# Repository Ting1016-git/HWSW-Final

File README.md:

# Smart Kitchen Guide

## Project Overview

**Smart Kitchen Guide** is a two-device cooking assistance system designed to help beginners master temperature control in cooking - from Chinese stir-frying to Western pan-searing. The system consists of a **Smart Handle Clip (Sensing Device)** that clamps onto any pan handle and monitors temperatures using triple sensing technology, and a **Cooking Terminal (Display Device)** that provides visual feedback through a stepper motor-driven gauge, LED indicators, and recipe guidance.

The sensing device wirelessly transmits temperature data to the display device, which uses a predictive algorithm to estimate when the target temperature will be reached and alerts the user at the optimal moment to add ingredients.

### Key Features

- **Triple Temperature Sensing**: Pan surface (IR), oil temperature (IR), and food internal temperature (K-type probe)
- **Universal Compatibility**: Spring-clip design fits handles from 15-40mm diameter
- **Open-Pan Cooking**: Perfect for stir-frying and sautéing without blocking the view
- **Wireless BLE Communication**: Real-time data transmission at 10Hz

### General Sketch

**Physical Features:**
- **Smart Handle Clip**: Spring-loaded clamp with OLED display, IR temperature sensor pointing toward pan body, detachable K-type thermocouple probe, and USB-C rechargeable battery
- **Cooking Terminal**: Retro radio-style desktop unit featuring a large circular temperature gauge with stepper motor-driven needle, RGB LED ring, OLED recipe display, and three tactile buttons (Select/Confirm/Back)

---

## Sensing Device: Smart Handle Clip

### Device Description

The Smart Handle Clip is a portable, clip-on temperature monitoring device that attaches to any pan or wok handle. It features **triple temperature sensing capability**:

1. **Infrared (IR) Sensor** - Non-contact measurement of pan surface and oil temperature
2. **K-Type Thermocouple Probe** - Detachable probe for measuring food internal temperature

The clip-on design allows the pan to remain open during cooking, making it ideal for Chinese stir-frying and Western sautéing where visual monitoring is essential.

### Detailed Sketch

### How It Works

1. **MLX90614 IR sensor** (mounted on bottom jaw, pointing toward pan) measures pan surface temperature from -70°C to +380°C without contact
2. The same IR sensor can measure **oil surface temperature** when the user aims it at the oil (mode switchable via button)
3. **Detachable K-type thermocouple probe** connects via port on the side for measuring food internal temperature (e.g., checking if meat is cooked through)
4. **MAX31855** thermocouple amplifier digitizes the probe signal via SPI
5. **ESP32-C3** microcontroller processes all sensor data at 10Hz and transmits via BLE
6. **0.96" OLED display** shows real-time temperature readings locally
7. **3 Status LEDs** indicate: Green (ready), Yellow (heating), Red (warning/overheat)
8. **500mAh Li-Po battery** provides ~8 hours of operation with USB-C charging

### Components & Part Numbers

| Component | Part Number | Description |
|-----------|-------------|-------------|
| Microcontroller | **ESP32-C3-MINI-1** | WiFi/BLE MCU, low power, SPI/I2C support |
| IR Temperature Sensor | **MLX90614ESF-BAA** | Non-contact IR thermometer, -70°C to +380°C, I2C |
| Thermocouple Sensor | **K-Type Thermocouple Probe** | Detachable, -50°C to +300°C, food-grade stainless steel |
| Thermocouple Amplifier | **MAX31855KASA+T** | Cold-junction compensated, SPI interface |
| OLED Display | **SSD1306 0.96" 128x64** | I2C interface, low power |
| Status LEDs | **0603 SMD LED** | Green, Yellow, Red (x3) |
| Battery | **Li-Po 502535** | 3.7V 500mAh rechargeable |
| Voltage Regulator | **AP2112K-3.3** | 3.3V LDO, 600mA output |
| Charging IC | **TP4056** | 1A Linear Li-ion charger, USB-C |
| Buttons | **TS-1109S** | 6x6mm SMD tact switch (x2: Power, Mode) |

## Display Device: Cooking Terminal

### Device Description

The Cooking Terminal is a desktop unit that receives temperature data from the Smart Handle Clip and provides rich visual feedback. The centerpiece is a large analog-style gauge with a stepper motor-driven needle showing current temperature. An RGB LED ring around the gauge indicates cooking status (heating/ready/overheating), while an OLED screen displays recipe steps and timing information. Users interact via three tactile buttons and can navigate through pre-loaded recipes.

### Detailed Sketch

### How It Works

1. The **ESP32-S3** receives temperature data via BLE from the Smart Handle Clip
2. Temperature prediction algorithm estimates time-to-target based on heating rate
3. The **28BYJ-48 stepper motor** drives the gauge needle to indicate current temperature (0-300°C scale)
4. **WS2812B RGB LED ring** shows status: blue (cold), green (heating), amber (target reached), red (overheating)
5. **1.3" OLED display** shows recipe name, current step, target temperature, and countdown timer
6. Three **tactile buttons** allow navigation: Select (◀), Confirm (✓), Back (↩)
7. **Buzzer** provides audio alerts when target temperature is reached
8. Powered by **18650 Li-ion battery** with USB-C charging

### Components & Part Numbers

| Component | Part Number | Description |
|-----------|-------------|-------------|
| Microcontroller | **ESP32-S3-WROOM-1** | Dual-core, BLE 5.0, sufficient GPIO |
| Stepper Motor | **28BYJ-48** | 5V unipolar, 64:1 gear ratio |
| Stepper Driver | **ULN2003A** | Darlington array driver |
| RGB LED Ring | **WS2812B 16-LED Ring** | Addressable RGB, 5V |
| OLED Display | **SH1106 1.3" 128x64** | I2C interface |
| Tactile Buttons | **TS-1109S** | 6x6mm SMD tact switch (x3) |
| Buzzer | **MLT-5020** | 5V active buzzer |
| Battery | **NCR18650B** | 3.7V 3400mAh Li-ion |
| Battery Charger | **TP4056 Module** | USB-C Li-ion charger with protection |
| Voltage Regulator | **AMS1117-3.3** | 3.3V LDO for logic |
| 5V Boost | **MT3608** | Step-up converter for motor/LED |

## System Communication & Architecture

### Communication Diagram

The Smart Handle Clip and Cooking Terminal communicate via **Bluetooth Low Energy (BLE)**:

- **Protocol**: BLE 5.0 with custom GATT service
- **Update Rate**: 10 Hz (100ms intervals)
- **Range**: Up to 10 meters (typical kitchen environment)
- **Latency**: < 50ms end-to-end

### System Block Diagram

```
┌─────────────────────────────────────────────────────────────────────────────────────┐
│                                 SYSTEM OVERVIEW                                     │
│                                                                                     │
│                                                                                     │
│    ┌──────────────────────┐                         ┌──────────────────────┐        │
│    │                      │                         │                      │        │
│    │   SENSING DEVICE     │      BLE 5.0 Link       │   DISPLAY DEVICE     │        │
│    │  (Smart Handle Clip) │ ═══════════════════════►│  (Cooking Terminal)  │        │
│    │                      │      10Hz, <50ms        │                      │        │
│    │                      │                         │                      │        │
│    └──────────────────────┘                         └──────────────────────┘        │
│                                                                                     │
│                                                                                     │
└─────────────────────────────────────────────────────────────────────────────────────┘
```

---

## Sensing Device (Smart Handle Clip)

```
┌─────────────────────────────────────────────────────────────────────────────────────┐
│                        SMART HANDLE CLIP (Sensing Device)                           │
│                                                                                     │
│                                                                                     │
│    ┌──────────────┐                             ┌──────────────┐                    │
│    │  MLX90614    │                             │ Xiao         │                    │
│    │  IR Sensor   ├──────────────┐      ┌───────┤ ESP32-C3     │                    │
│    │  (I2C)       │              │      │       │ (BLE TX)     │                    │
│    └──────────────┘              │      │       └───────┬──────┘                    │
│                                  │      │               │                           │
│                                  ▼      ▼               │                           │
│                              ┌──────────────┐           │          BLE 5.0          │
│                              │              │           │         ════════►         │
│                              │  Processing  │◄──────────┘                           │
│                              │              │                                       │
│                              └──────┬───────┘                                       │
│                                     │                                               │
│                           ┌─────────┴─────────┐                                     │
│                           │                   │                                     │
│                           ▼                   ▼                                     │
│                    ┌──────────────┐    ┌──────────────┐                             │
│                    │  WS2812B     │    │   Rotary     │                             │
│                    │  RGB LED     │    │   Encoder    │                             │
│                    │  (x1)        │    │   (EC11)     │                             │
│                    └──────────────┘    └──────────────┘                             │
│                                                                                     │
│                                                                                     │
│    ┌──────────────┐         ┌──────────────────────────────────────┐                │
│    │  Li-Po       │         │      Xiao ESP32-C3 Built-in          │                │
│    │  500mAh      ├────────►│  ┌────────────┐    ┌────────────┐    │                │
│    │  3.7V        │         │  │  TP4056    │    │   3.3V     │    │                │
│    └──────────────┘         │  │  Charger   │    │   LDO      │    │                │
│           ▲                 │  └──────┬─────┘    └──────┬─────┘    │                │
│           │                 │         │                 │          │                │
│       USB-C ────────────────┼─────────┘                 └──────────┼───► 3.3V       │
│                             │                                      │                │
│                             └──────────────────────────────────────┘                │
│                                                                                     │
│                                                                                     │
└─────────────────────────────────────────────────────────────────────────────────────┘
```

---

## Display Device (Cooking Terminal)

```
┌─────────────────────────────────────────────────────────────────────────────────────┐
│                        COOKING TERMINAL (Display Device)                            │
│                                                                                     │
│                                              │                                      │
│                                              │ BLE 5.0                              │
│                                              ▼                                      │
│                                      ┌──────────────┐                               │
│                              ┌───────┤ Xiao         │                               │
│                              │       │ ESP32-C3     ├───────┐                       │
│                              │       │ (BLE RX)     │       │                       │
│                              │       └──────────────┘       │                       │
│                              │               │              │                       │
│                              │               │              │                       │
│      ┌───────────────────────┼───────────────┼──────────────┼───────────────┐       │
│      │                       │               │              │               │       │
│      ▼                       ▼               ▼              ▼               ▼       │
│ ┌──────────┐ ┌──────────┐ ┌──────────┐ ┌──────────┐ ┌──────────┐ ┌──────────┐       │
│ │ ULN2003A │ │ WS2812B  │ │ SH1106   │ │ Rotary   │ │ Piezo    │ │ Temp     │       │
│ │ Driver   │ │ RGB Ring │ │ OLED     │ │ Encoder  │ │ Buzzer   │ │ Predict  │       │
│ │          │ │ (x8)     │ │ 1.3"     │ │ (EC11)   │ │          │ │ Algo     │       │
│ └────┬─────┘ └──────────┘ └──────────┘ └──────────┘ └──────────┘ └──────────┘       │
│      │                                                                              │
│      ▼                                                                              │
│ ┌──────────┐                                                                        │
│ │ 28BYJ-48 │                                                                        │
│ │ Stepper  │                                                                        │
│ │ Motor    │                                                                        │
│ └────┬─────┘                                                                        │
│      │                                                                              │
│      ▼                                                                              │
│ ┌──────────┐                                                                        │
│ │ Gauge    │                                                                        │
│ │ Needle   │                                                                        │
│ └──────────┘                                                                        │
│                                                                                     │
│                                                                                     │
│    ┌──────────────┐       ┌──────────────┐                                          │
│    │  18650       │       │   TP4056     │◄──── USB-C                               │
│    │  Battery     ├──────►│   Charger    │                                          │
│    │  3400mAh     │       │   (Xiao)     │                                          │
│    └──────────────┘       └───────┬──────┘                                          │
│                                   │                                                 │
│                    ┌──────────────┴──────────────┐                                  │
│                    │                             │                                  │
│                    ▼                             ▼                                  │
│            ┌──────────────┐             ┌──────────────┐                            │
│            │  Xiao 3.3V   │             │   MT3608     │                            │
│            │  LDO         │             │   Boost      │                            │
│            └───────┬──────┘             └───────┬──────┘                            │
│                    │                            │                                   │
│                    ▼                            ▼                                   │
│              3.3V (Logic)                 5V (Motor/LED)                            │
│              • Xiao MCU                   • ULN2003A                                │
│              • SH1106 OLED                • 28BYJ-48                                │
│              • Rotary Encoder             • WS2812B                                 │
│                                           • Piezo Buzzer                            │
│                                                                                     │
└─────────────────────────────────────────────────────────────────────────────────────┘
```

---

## Complete System Block Diagram

```
┌─────────────────────────────────────────────────────────────────────────────────────┐
│                        SMART HANDLE CLIP (Sensing Device)                           │
│                                                                                     │
│    ┌──────────────┐              ┌──────────────┐        ┌──────────────┐           │
│    │  MLX90614    │    I2C       │              │        │  WS2812B     │           │
│    │  IR Sensor   ├─────────────►│ Xiao         │◄───────┤  RGB LED     │           │
│    └──────────────┘              │ ESP32-C3     │        │  (x1)        │           │
│                                  │              │        └──────────────┘           │
│    ┌──────────────┐    GPIO      │ (BLE TX)     │        ┌──────────────┐           │
│    │  Rotary      ├─────────────►│              │        │  Li-Po       │           │
│    │  Encoder     │              └───────┬──────┘        │  500mAh      │           │
│    └──────────────┘                      │               └───────┬──────┘           │
│                                          │                       │                  │
│                                          │ BLE 5.0               │ Power            │
│                                          │                       ▼                  │
│                                          │               ┌──────────────┐           │
│                                          │               │ Xiao Built-in│           │
│                                          │               │ Charger+LDO  │◄── USB-C  │
│                                          │               └──────────────┘           │
│                                          │                       │                  │
│                                          │                       ▼                  │
│                                          │                    3.3V Out              │
└──────────────────────────────────────────┼──────────────────────────────────────────┘
                                           │
                                           │
                        ═══════════════════╪═══════════════════
                              Wireless     │     Communication
                        ═══════════════════╪═══════════════════
                                           │
                                           │
┌──────────────────────────────────────────┼──────────────────────────────────────────┐
│                        COOKING TERMINAL (Display Device)                            │
│                                          │                                          │
│                                          ▼                                          │
│    ┌──────────────────────────────────────────────────────────────────────────┐     │
│    │                            Xiao ESP32-C3                                 │     │
│    │                              (BLE RX)                                    │     │
│    │                                                                          │     │
│    │    ┌──────────────┐                                                      │     │
│    │    │    Temp      │                                                      │     │
│    │    │   Predict    │                                                      │     │
│    │    │    Algo      │                                                      │     │
│    │    └──────────────┘                                                      │     │
│    │                                                                          │     │
│    └───┬────────┬────────┬────────┬────────┬────────┬─────────────────────────┘     │
│        │        │        │        │        │        │                               │
│        ▼        ▼        ▼        ▼        ▼        ▼                               │
│   ┌────────┐┌────────┐┌────────┐┌────────┐┌────────┐┌────────┐                      │
│   │ULN2003A││WS2812B ││SH1106  ││Rotary  ││Piezo   ││        │                      │
│   │ Driver ││RGB Ring││OLED    ││Encoder ││Buzzer  ││        │                      │
│   └───┬────┘│ (x8)   ││ 1.3"   │└────────┘└────────┘│        │                      │
│       │     └────────┘└────────┘                    │        │                      │
│       ▼                                             │        │                      │
│   ┌────────┐                                        │        │                      │
│   │28BYJ-48│                                        │        │                      │
│   │Stepper │                                        │        │                      │
│   │ Motor  │                                        │        │                      │
│   └───┬────┘                                        │        │                      │
│       │                                             │        │                      │
│       ▼                                             │        │                      │
│   ┌────────┐                                        │        │                      │
│   │ Gauge  │                                        │        │                      │
│   │ Needle │                                        │        │                      │
│   └────────┘                                        │        │                      │
│                                                     │        │                      │
│                                                     │        │                      │
│    ┌──────────────┐      ┌──────────────┐           │        │                      │
│    │   18650      │      │   Xiao       │◄── USB-C  │        │                      │
│    │   Battery    ├─────►│   Charger    │           │        │                      │
│    │   3400mAh    │      └───────┬──────┘           │        │                      │
│    └──────────────┘              │                  │        │                      │
│                                  │                  │        │                      │
│                    ┌─────────────┴─────────────┐    │        │                      │
│                    │                           │    │        │                      │
│                    ▼                           ▼    │        │                      │
│            ┌──────────────┐            ┌──────────────┐      │                      │
│            │    3.3V      │            │   MT3608     │      │                      │
│            │    LDO       │            │   5V Boost   │      │                      │
│            └───────┬──────┘            └───────┬──────┘      │                      │
│                    │                           │             │                      │
│                    ▼                           ▼             │                      │
│               3.3V (Logic)                5V (Motor/LED)     │                      │
│                                                              │                      │
└─────────────────────────────────────────────────────────────────────────────────────┘
```

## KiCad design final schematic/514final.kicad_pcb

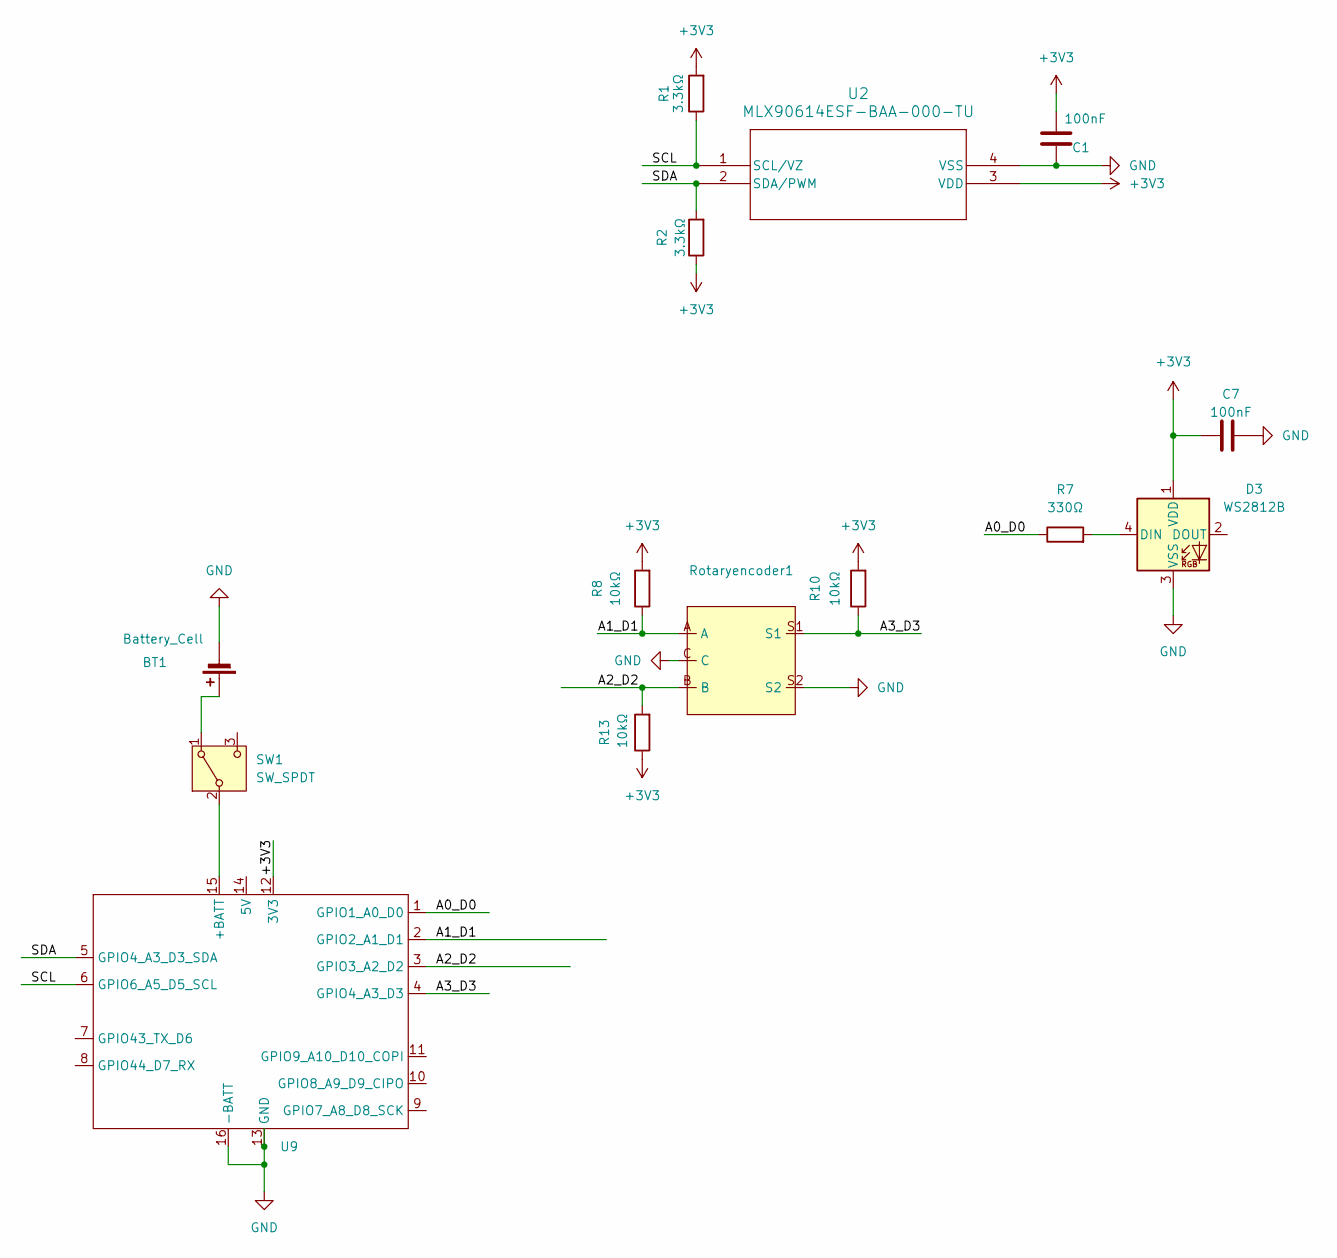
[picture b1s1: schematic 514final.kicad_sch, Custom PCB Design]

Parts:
BT1: Battery_Cell; PinSocket_1x02_P2.54mm_Vertical
C1, C7: 100nF; C_0603_1608Metric_Pad1.08x0.95mm_HandSolder
D3: WS2812B; LED_WS2812B_PLCC4_5.0x5.0mm_P3.2mm
R1, R2: 3.3kΩ; R_0603_1608Metric_Pad0.98x0.95mm_HandSolder
R7: 330Ω; R_0603_1608Metric_Pad0.98x0.95mm_HandSolder
R8, R10, R13: 10kΩ; R_0603_1608Metric_Pad0.98x0.95mm_HandSolder
Rotaryencoder1: RotaryEncoder_Alps_EC11E-Switch_Vertical_H20mm_CircularMoun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
SW1: SW_SPDT; PinSocket_1x03_P2.54mm_Vertical
U2: MLX90614ESF-BAA-000-TU; MLX90614ESF-BAA_MEL
U9: XIAO_ESP32

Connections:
+3V3: C1.1, C7.1, D3.1 (VDD), R1.2, R2.1, R8.2, R10.2, R13.1, U2.3 (VDD), U9.12 (3V3)
/A0_D0: R7.1, U9.1 (GPIO1_A0_D0)
/A1_D1: R8.1, Rotaryencoder1.A, U9.2 (GPIO2_A1_D1)
/A2_D2: R13.2, Rotaryencoder1.B, U9.3 (GPIO3_A2_D2)
/A3_D3: R10.1, Rotaryencoder1.S1, U9.4 (GPIO4_A3_D3)
/SCL: R1.1, U2.1 (SCL/VZ), U9.6 (GPIO6_A5_D5_SCL)
/SDA: R2.2, U2.2 (SDA/PWM), U9.5 (GPIO4_A3_D3_SDA)
GND: BT1.2 (-), C1.2, C7.2, D3.3 (VSS), Rotaryencoder1.C, Rotaryencoder1.S2, U2.4 (VSS), U9.13 (GND), U9.16 (-BATT)
unnamed: BT1.1 (+), SW1.1 (A)
unnamed: D3.4 (DIN), R7.2
unnamed: SW1.2 (B), U9.15 (+BATT)

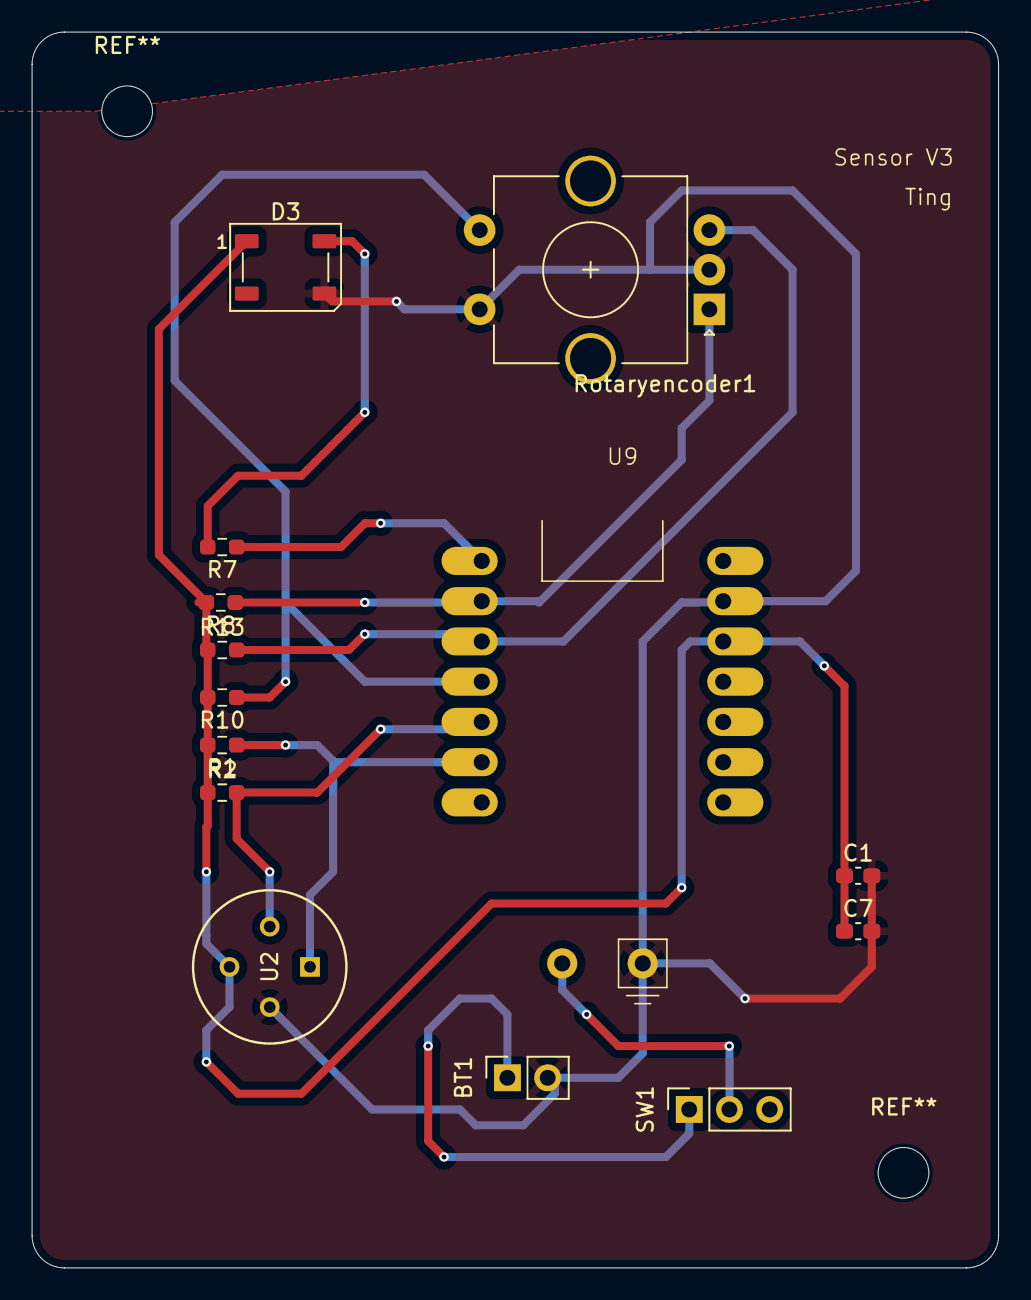
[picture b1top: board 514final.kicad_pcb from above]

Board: 2 copper layers, 61.0 x 78.0 mm, 14 parts (0 on the bottom side), 11 nets.

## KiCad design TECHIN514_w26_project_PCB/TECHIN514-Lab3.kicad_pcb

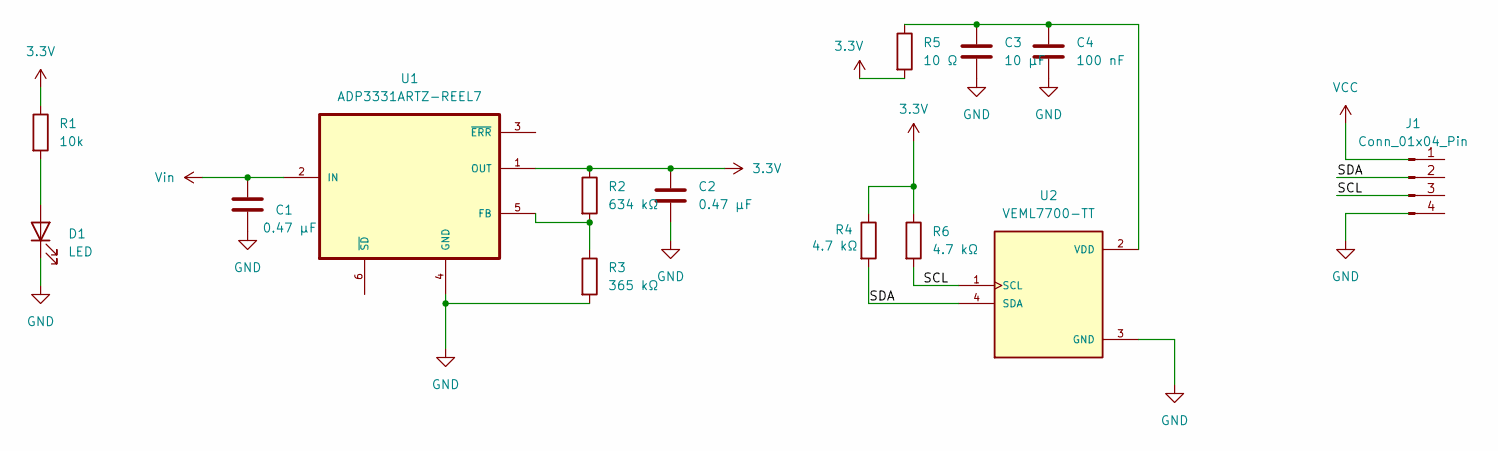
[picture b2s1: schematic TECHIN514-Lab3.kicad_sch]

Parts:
C1, C2: 0.47 µF; C_0603_1608Metric_Pad1.08x0.95mm_HandSolder
C3: 10 µF; C_0603_1608Metric_Pad1.08x0.95mm_HandSolder
C4: 100 nF; C_0603_1608Metric_Pad1.08x0.95mm_HandSolder
D1: LED; LED_0603_1608Metric_Pad1.05x0.95mm_HandSolder
J1: Conn_01x04_Pin; PinSocket_1x04_P2.54mm_Vertical
R1: 10k; R_0603_1608Metric_Pad0.98x0.95mm_HandSolder
R2: 634 kΩ; R_0603_1608Metric_Pad0.98x0.95mm_HandSolder
R3: 365 kΩ; R_0603_1608Metric_Pad0.98x0.95mm_HandSolder
R4, R6: 4.7 kΩ; R_0603_1608Metric_Pad0.98x0.95mm_HandSolder
R5: 10 Ω; R_0603_1608Metric_Pad0.98x0.95mm_HandSolder
U1: ADP3331ARTZ-REEL7; SOT95P280X145-6N
U2: VEML7700-TT; XDCR_VEML7700-TT; PARTREV 1.6

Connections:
3.3V: C2.1, R1.1, R2.1, R4.1, R5.2, R6.1, U1.1 (OUT)
/SCL: J1.2, R6.2, U2.1 (SCL)
/SDA: J1.3, R4.2, U2.4 (SDA)
GND: C1.2, C2.2, C3.2, C4.2, D1.1 (K), J1.1, R3.2, U1.4 (GND), U2.3 (GND)
unnamed: D1.2 (A), R1.2
unnamed: R2.2, R3.1, U1.5 (FB)
unnamed: C3.1, C4.1, R5.1, U2.2 (VDD)
VCC: C1.1, J1.4, U1.2 (IN)

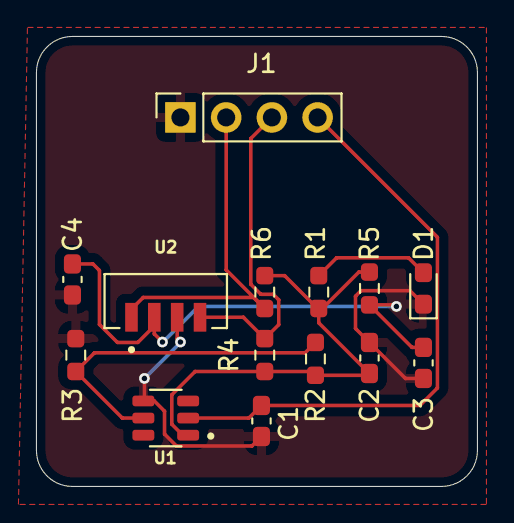
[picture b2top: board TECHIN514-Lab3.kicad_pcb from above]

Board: 2 copper layers, 24.5 x 25.0 mm, 14 parts (0 on the bottom side), 8 nets.

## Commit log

2026-01-20 submit README
2026-01-20 update readme name
2026-01-27 update architecture
2026-01-30 finish pcb design
2026-02-07 update battery and datasheet link
2026-03-02 add second device code
